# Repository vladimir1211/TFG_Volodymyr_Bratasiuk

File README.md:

# TFG_Volodymyr_Bratasiuk
Este repositorio contiene diseños de las PCBs generados para mi TFG durante la segunda mitad del 2022.

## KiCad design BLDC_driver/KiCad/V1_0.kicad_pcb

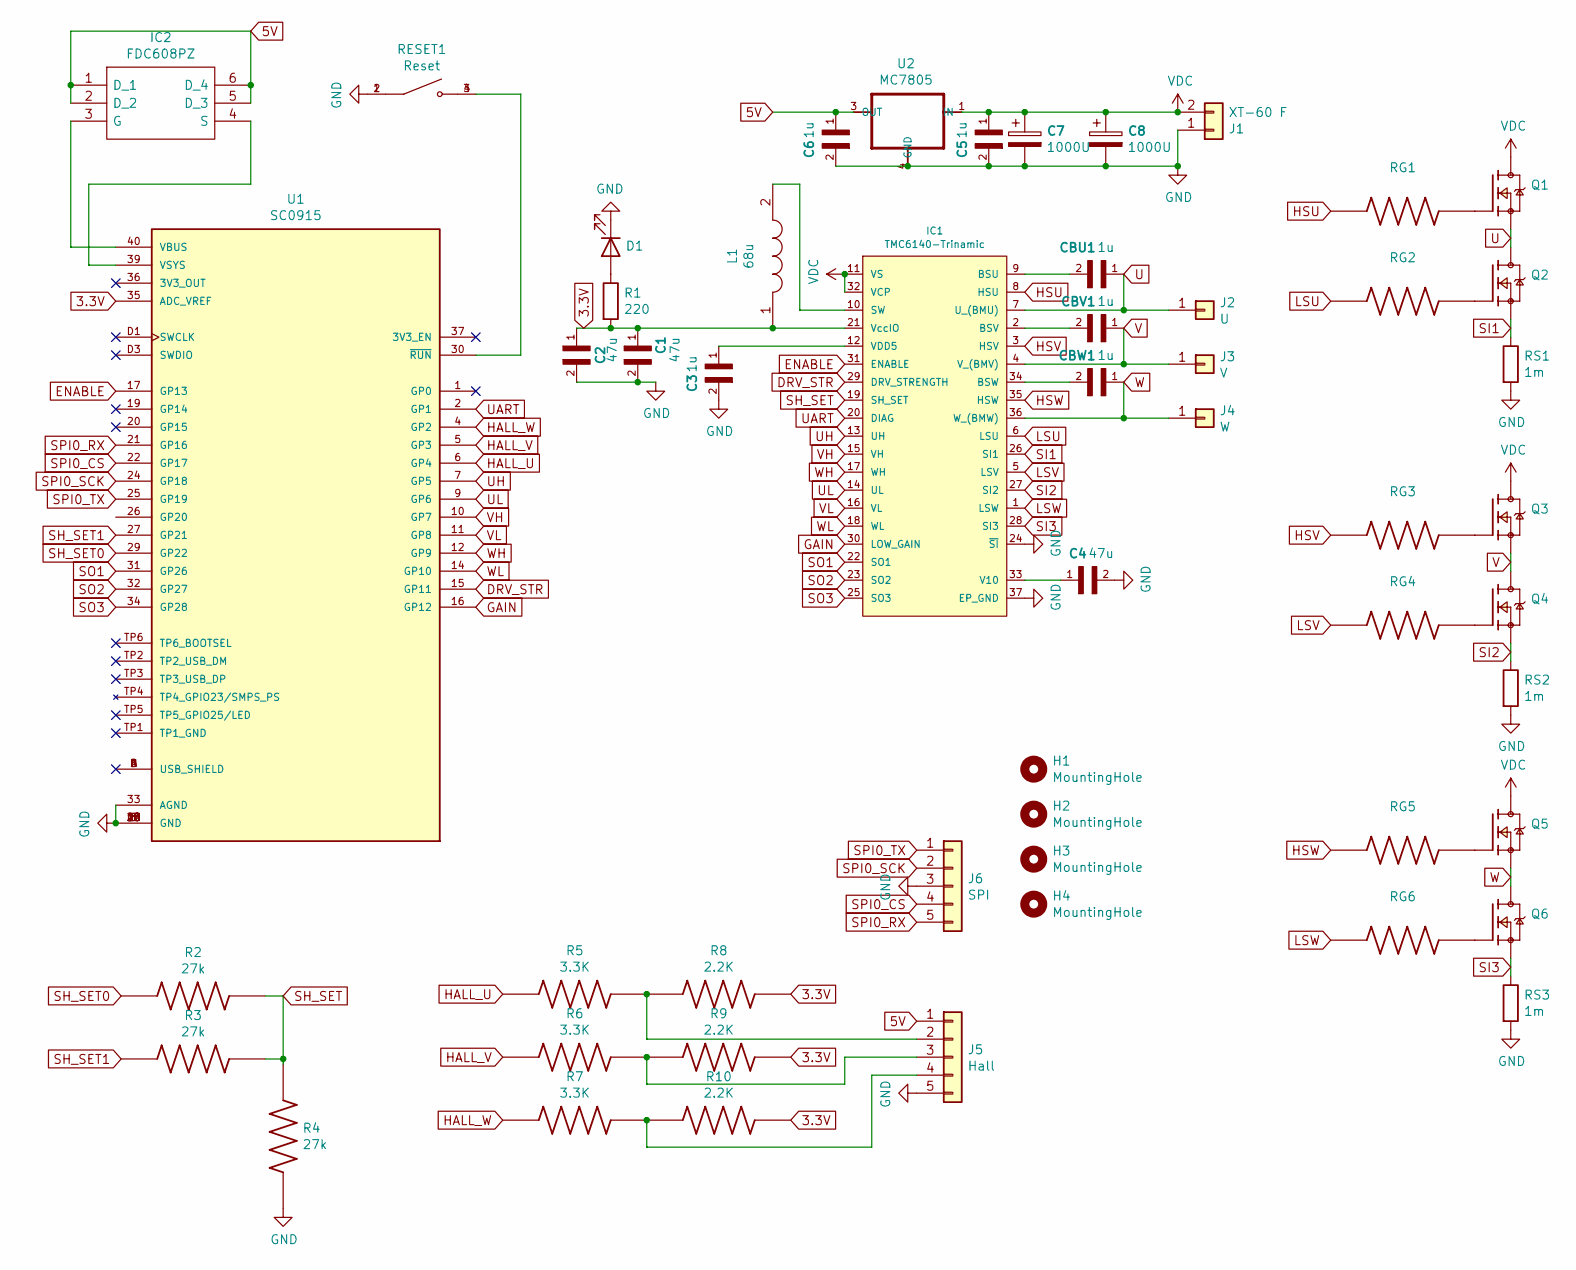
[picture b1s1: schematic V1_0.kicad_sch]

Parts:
C1, C2, C4: 47u; CAPC3225X270N
C3, C5, C6: 1u; CAPC2012X140N
C7, C8: 1000U; CP_Radial_D16.0mm_P7.50mm
CBU1: 1u; CAPC2012X140N
CBV1: 1u; CAPC2012X140N
CBW1: 1u; CAPC2012X140N
D1: LED; LED_D3.0mm
H1, H2, H3, H4: MountingHole; MountingHole_3.2mm_M3
IC1: TMC6140-Trinamic; QFN-36-1EP_5x6mm_P0.5mm_EP3.6x4.1mm_ThermalVias
IC2: FDC608PZ; SOT95P275X110-6N; Manufacturer_Part_Number FDC608PZ
J1: XT-60 F; AMASS_XT60-F_1x02_P7.20mm_Vertical
J2: U; MountingHole_2.2mm_M2_Pad_Via
J3: V; MountingHole_2.2mm_M2_Pad_Via
J4: W; MountingHole_2.2mm_M2_Pad_Via
J5: Hall; PinHeader_1x05_P2.54mm_Vertical
J6: SPI; PinHeader_1x05_P2.54mm_Vertical
L1: 68u; NPIS27H680MTRF; Manufacturer_Part_Number NPIS27H680MTRF
Q1, Q2, Q3, Q4, Q5, Q6: IAUS300N08S5N012ATMA1; IFX-PG-HSOG-8-1-V; PARTREV 1.0
R1: 220; R_Axial_DIN0207_L6.3mm_D2.5mm_P7.62mm_Horizontal
R2, R3, R4: 27k; RESC1508X50N
R5, R6, R7: 3.3K; RESC1608X55N
R8, R9, R10: 2.2K; RESC1608X55N; Voltage_Rating 50 V; Tolerance 1%
RESET1: Reset; SW_1571563-1
RG1, RG2, RG3, RG4, RG5, RG6: CRL1206-FW-1R00ELF; RESC3216X70N
RS1, RS2, RS3: 1m; RESC6331X70N
U1: SC0915; MODULE_SC0915; PARTREV 1.6
U2: MC7805; TO229P990X238-4N

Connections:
3.3V: C1.1, C2.1, IC1.21 (VccIO), L1.1, R1.2, R8.2, R9.2, R10.2, U1.35 (ADC_VREF)
5V: C6.1, IC2.1 (D_1), IC2.2 (D_2), IC2.5 (D_3), IC2.6 (D_4), J5.1, U2.3 (OUT)
DRV_STR: IC1.29 (DRV_STRENGTH), U1.15 (GP11)
ENABLE: IC1.31 (ENABLE), U1.17 (GP13)
GAIN: IC1.30 (LOW_GAIN), U1.16 (GP12)
GND: C1.2, C2.2, C3.2, C4.2, C5.2, C6.2, C7.2, C8.2, D1.1 (K), IC1.24 (~SI), IC1.37 (EP_GND), J1.1, J5.5, J6.3, R4.1, RESET1.1, RESET1.2, RS1.2, RS2.2, RS3.2, U1.3 (GND), U1.8 (GND), U1.13 (GND), U1.18 (GND), U1.23 (GND), U1.28 (GND), U1.33 (AGND), U1.38 (GND), U1.D2 (GND), U2.4 (GND)
HALL_U: R5.1, U1.6 (GP4)
HALL_V: R6.1, U1.5 (GP3)
HALL_W: R7.1, U1.4 (GP2)
HSU: IC1.8 (HSU), RG1.1
HSV: IC1.3 (HSV), RG3.1
HSW: IC1.35 (HSW), RG5.1
LSU: IC1.6 (LSU), RG2.1
LSV: IC1.5 (LSV), RG4.1
LSW: IC1.1 (LSW), RG6.1
unnamed: C3.1, IC1.12 (VDD5)
unnamed: C4.1, IC1.33 (V10)
unnamed: CBU1.2, IC1.9 (BSU)
unnamed: CBV1.2, IC1.2 (BSV)
unnamed: CBW1.2, IC1.34 (BSW)
unnamed: D1.2 (A), R1.1
unnamed: IC1.10 (SW), L1.2
unnamed: IC2.3 (G), U1.40 (VBUS)
unnamed: IC2.4 (S), U1.39 (VSYS)
unnamed: J5.2, R5.2, R8.1
unnamed: J5.3, R6.2, R9.1
unnamed: J5.4, R7.2, R10.1
unnamed: Q1.1, RG1.2
unnamed: Q2.1, RG2.2
unnamed: Q3.1, RG3.2
unnamed: Q4.1, RG4.2
unnamed: Q5.1, RG5.2
unnamed: Q6.1, RG6.2
unnamed: RESET1.3, RESET1.4, U1.30 (~RUN)
SH_SET: IC1.19 (SH_SET), R2.2, R3.2, R4.2
SH_SET0: R2.1, U1.29 (GP22)
SH_SET1: R3.1, U1.27 (GP21)
SI1: IC1.26 (SI1), Q2.2, Q2.3, Q2.4, Q2.5, Q2.6, Q2.7, Q2.8, RS1.1
SI2: IC1.27 (SI2), Q4.2, Q4.3, Q4.4, Q4.5, Q4.6, Q4.7, Q4.8, RS2.1
SI3: IC1.28 (SI3), Q6.2, Q6.3, Q6.4, Q6.5, Q6.6, Q6.7, Q6.8, RS3.1
SO1: IC1.22 (SO1), U1.31 (GP26)
SO2: IC1.23 (SO2), U1.32 (GP27)
SO3: IC1.25 (SO3), U1.34 (GP28)
SPI0_CS: J6.4, U1.22 (GP17)
SPI0_RX: J6.5, U1.21 (GP16)
SPI0_SCK: J6.2, U1.24 (GP18)
SPI0_TX: J6.1, U1.25 (GP19)
U: CBU1.1, IC1.7 (U_(BMU)), J2.1, Q1.2, Q1.3, Q1.4, Q1.5, Q1.6, Q1.7, Q1.8, Q2.9
UART: IC1.20 (DIAG), U1.2 (GP1)
UH: IC1.13 (UH), U1.7 (GP5)
UL: IC1.14 (UL), U1.9 (GP6)
V: CBV1.1, IC1.4 (V_(BMV)), J3.1, Q3.2, Q3.3, Q3.4, Q3.5, Q3.6, Q3.7, Q3.8, Q4.9
VDC: C5.1, C7.1, C8.1, IC1.11 (VS), IC1.32 (VCP), J1.2, Q1.9, Q3.9, Q5.9, U2.1 (IN)
VH: IC1.15 (VH), U1.10 (GP7)
VL: IC1.16 (VL), U1.11 (GP8)
W: CBW1.1, IC1.36 (W_(BMW)), J4.1, Q5.2, Q5.3, Q5.4, Q5.5, Q5.6, Q5.7, Q5.8, Q6.9
WH: IC1.17 (WH), U1.12 (GP9)
WL: IC1.18 (WL), U1.14 (GP10)

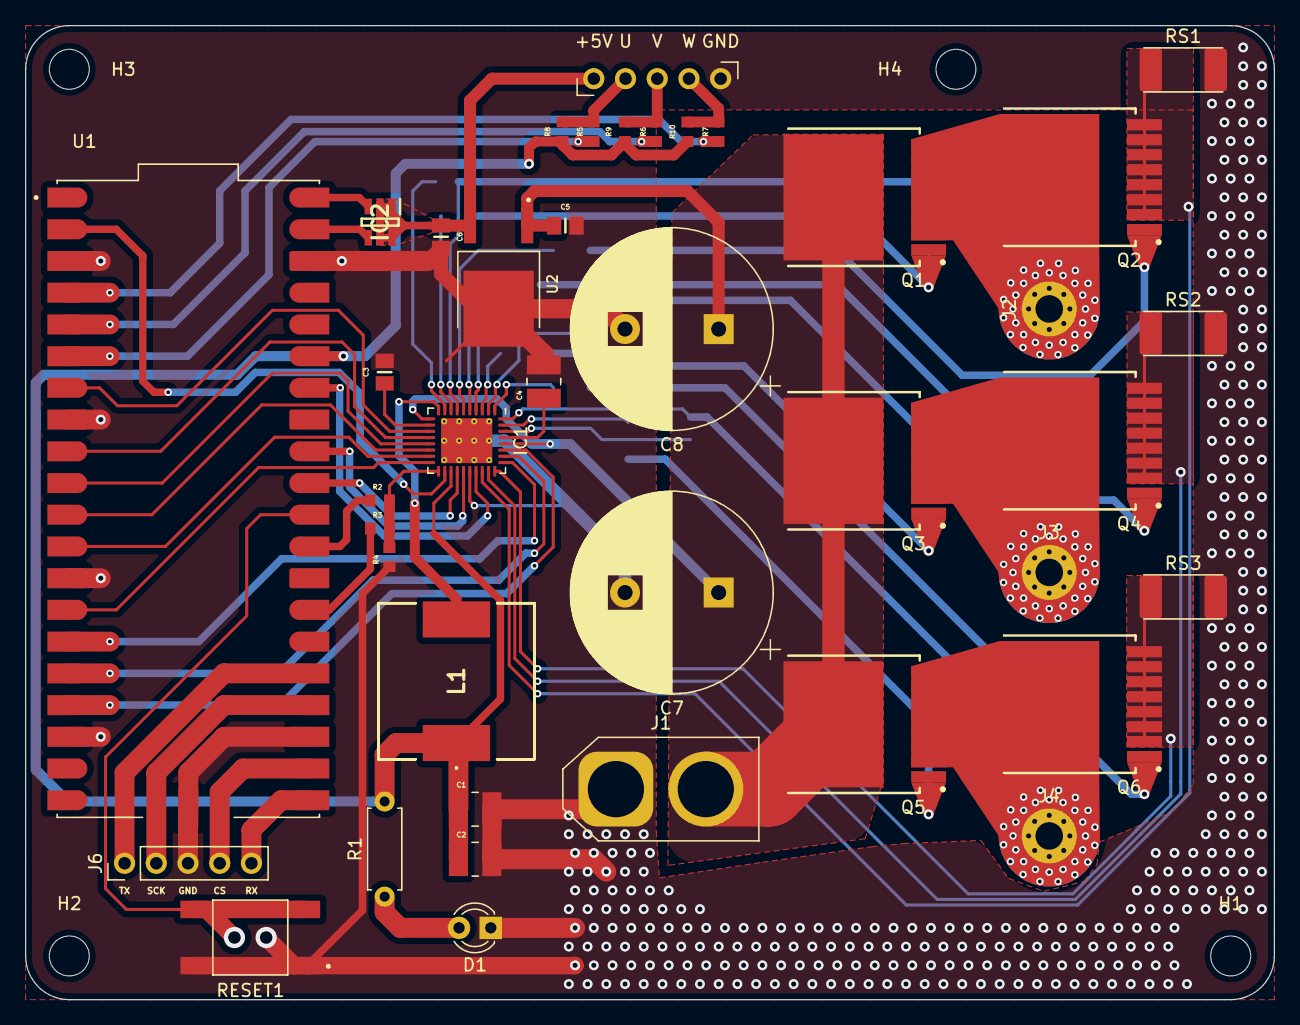
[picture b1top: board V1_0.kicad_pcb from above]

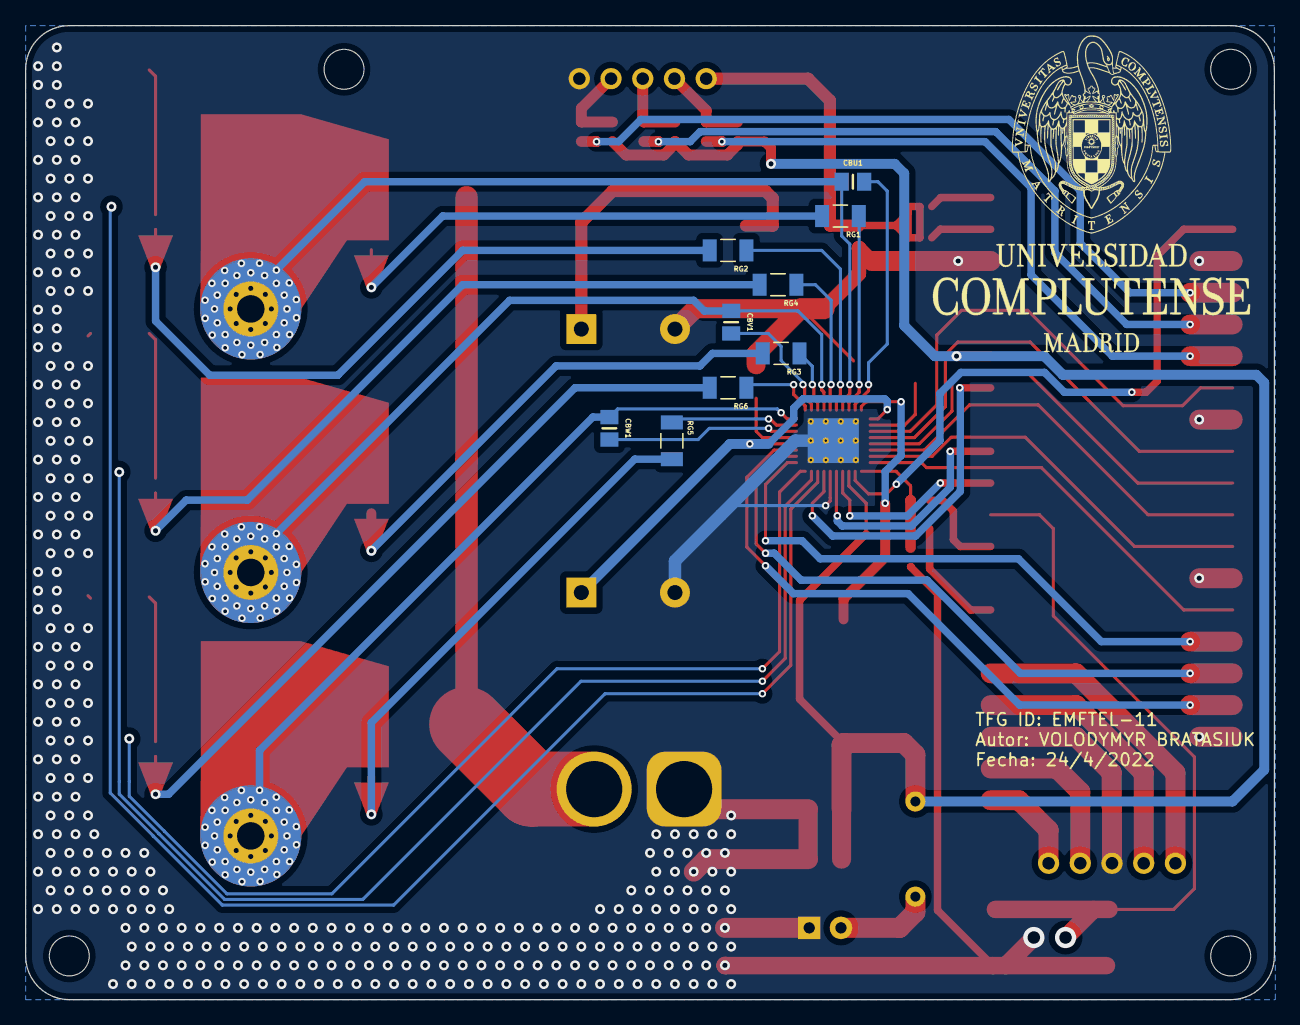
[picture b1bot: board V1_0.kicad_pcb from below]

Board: 2 copper layers, 100.0 x 78.0 mm, 53 parts (9 on the bottom side), 58 nets.

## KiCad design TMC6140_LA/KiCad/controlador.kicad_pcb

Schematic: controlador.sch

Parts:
IC1: TMC6140-Trinamic; QFN-36-1EP_5x6mm_P0.5mm_EP3.6x4.1mm_ThermalVias
J1, J2: Conn_01x19; PinHeader_1x19_P2.54mm_Vertical

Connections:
1: IC1.1, J1.1
2: IC1.2, J1.2
3: IC1.3, J1.3
4: IC1.4, J1.4
5: IC1.5, J1.5
6: IC1.6, J1.6
7: IC1.7, J1.7
8: IC1.8, J1.8
9: IC1.9, J1.9
10: IC1.10, J1.10
11: IC1.11, J1.11
12: IC1.12, J1.12
13: IC1.13, J1.13
14: IC1.14, J1.14
15: IC1.15, J1.15
16: IC1.16, J1.16
17: IC1.17, J1.17
18: IC1.18, J1.18
19: IC1.19, J2.19
20: IC1.20, J2.18
21: IC1.21, J2.17
22: IC1.22, J2.16
23: IC1.23, J2.15
24: IC1.24, J2.14
25: IC1.25, J2.13
26: IC1.26, J2.12
27: IC1.27, J2.11
28: IC1.28, J2.10
29: IC1.29, J2.9
30: IC1.30, J2.8
31: IC1.31, J2.7
32: IC1.32, J2.6
33: IC1.33, J2.5
34: IC1.34, J2.4
35: IC1.35, J2.3
36: IC1.36, J2.2
GND: IC1.37, J1.19, J2.1

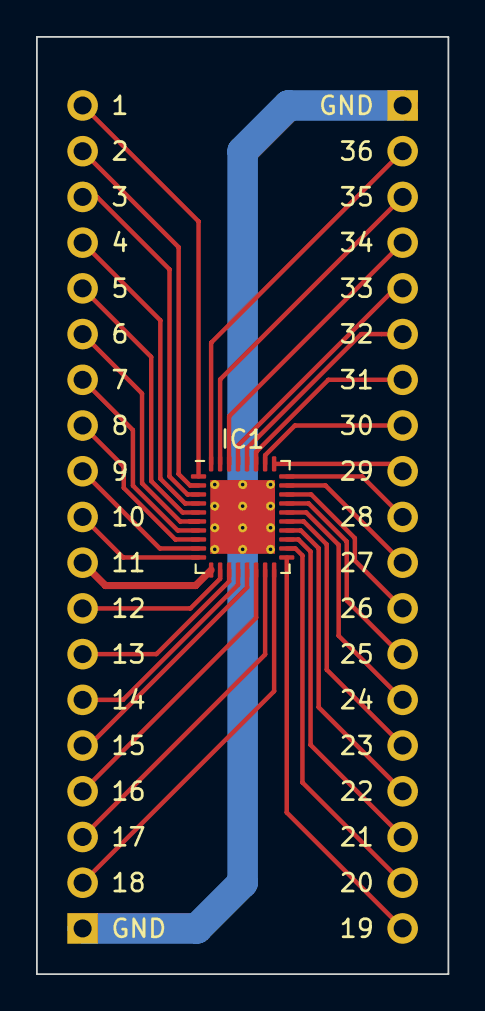
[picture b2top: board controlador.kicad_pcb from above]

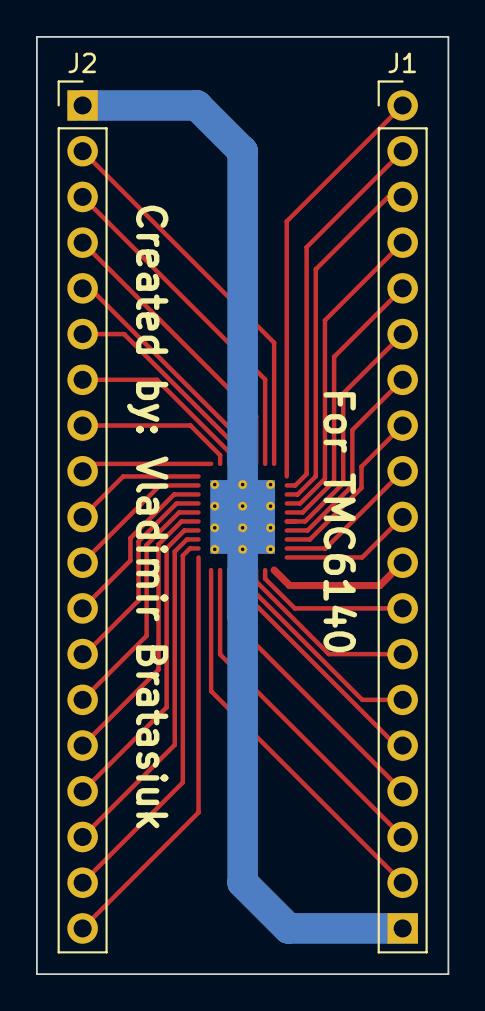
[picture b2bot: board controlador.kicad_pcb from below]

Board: 2 copper layers, 22.9 x 52.1 mm, 3 parts (2 on the bottom side), 37 nets.

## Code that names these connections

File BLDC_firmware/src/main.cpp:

// Motor phases pins
//-----------------------------------------------------------------------------
#define HU  5   // High-side switch U
#define LU  6   // Low-side switch U
#define HV  7   // High-side switch V
#define LV  8   // Low-side switch V
#define HW  9   // High-side switch W
#define LW  10  // Low-side switch W
//-----------------------------------------------------------------------------

// Hall sensor pins
//-----------------------------------------------------------------------------
#define HALL_U 2  // Hall sensor phase U
#define HALL_V 3  // Hall sensor phase V
#define HALL_W 4  // Hall sensor phase W
//-----------------------------------------------------------------------------

// Pins for aditional control of TMC6140-LA
//-----------------------------------------------------------------------------
#define DRV_STR 11      //Set to 1: 0.5A / Set to 0: 1A
#define GAIN 12         //Set to 1: gain 50x / Set to 0: gain 20x
#define ENABLE_PIN 13   //Set to 1: enable / Set to 0: disable
#define SH_0 22         //Set to 1: short to ground / Set to 0: no short
#define SH_1 21         //Set to 1: short to ground / Set to 0: no short
//------------------------------------------------------------------------------

//
#define PP 15 // Pole pairs
//
#define LED 25 // LED pin

#include <SimpleFOC.h>


// Hall sensor instance
// HallSensor(int hallA, int hallB , int cpr, int index)
//  - hallA, hallB, hallC    - HallSensor A, B and C pins
//  - pp                     - pole pairs
HallSensor sensor = HallSensor(HALL_U, HALL_V, HALL_W, PP);

// Interrupt routine intialisation
// channel A and B callbacks
void doA(){sensor.handleA();}
void doB(){sensor.handleB();}
void doC(){sensor.handleC();}

// BLDC driver instance
//  BLDCDriver6PWM( int phA_h, int phA_l, int phB_h, int phB_l, int phC_h, int phC_l, int en)
//  - phA_h, phA_l - A phase pwm pin high/low pair 
//  - phB_h, phB_l - B phase pwm pin high/low pair
//  - phB_h, phC_l - C phase pwm pin high/low pair
//  - enable pin    - (optional input)
BLDCDriver6PWM driver = BLDCDriver6PWM(HU, LU, HV, LV, HW, LW, ENABLE_PIN);
// BLDCMotor motor = BLDCMotor(pole pair number);
BLDCMotor motor = BLDCMotor(PP);

// velocity set point variable
float target_velocity = 5;
// include commander interface
Commander command = Commander(Serial);
void doMotor(char* cmd) { command.motor(&motor, cmd); }


void receiveEvent(int bytes) {

  digitalWrite(LED, HIGH);
  

  int x = Wire.read();    // read one character from the I2C
  
  motor.move(x);

  Serial.print( x);
  Serial.print( "\n");
  digitalWrite(LED, LOW);
}
void seti2c() {
  // Define the LED pin as Output
  pinMode (LED, OUTPUT);
  delay(500);
  // Start the I2C Bus as Slave on address 9
  Wire.begin(9); 
  // Attach a function to trigger when something is received.
  Wire.onReceive(receiveEvent);
}

void mode0() {
  // Set the motor to mode 0
  motor.PID_velocity.P = 0.1;
  motor.PID_velocity.I = 0.5;
  motor.PID_velocity.D = 0;
  motor.voltage_limit = 4;
  Serial.print("MODE 0 SET\n");
}

void mode1() {
  // Set the motor to mode 1
  motor.PID_velocity.P = 0.3;
  motor.PID_velocity.I = 1;
  motor.PID_velocity.D = 0;
  motor.voltage_limit = 8;
  Serial.print("MODE 1 SET\n");
}

void mode2() {
  // Set the motor to mode 2
  motor.PID_velocity.P = 0.9;
  motor.PID_velocity.I = 2;
  motor.PID_velocity.D = 0;
  motor.voltage_limit = 10;
  Serial.print("MODE 2 SET\n");
}

void change_mode(char* cmd) {
  if (cmd[0] == '0') {
    mode0();
  } else if (cmd[0] == '1') {
    mode1();
  } else if (cmd[0] == '2') {
    mode2();
  }
}

void disable_enable(char* cmd) {
  if (cmd[0] == '0') {
    digitalWrite(SH_0, LOW);
    digitalWrite(SH_1, LOW);
    motor.linkSensor(nullptr);
    
    // motor.move(0);
    Serial.print("DISABLE\n");
  } else if (cmd[0] == '1') {
    digitalWrite(SH_0, HIGH);
    digitalWrite(SH_1, HIGH);
    motor.linkSensor(&sensor);
    Serial.print("ENABLE\n");
  }
}


void setup(){

seti2c();

pinMode(DRV_STR, OUTPUT);
pinMode(GAIN, OUTPUT);
pinMode(ENABLE_PIN, OUTPUT);
pinMode(SH_0, OUTPUT);
pinMode(SH_1, OUTPUT);

digitalWrite(ENABLE_PIN, HIGH);
digitalWrite(DRV_STR, LOW);
digitalWrite(GAIN, LOW);
digitalWrite(SH_0, HIGH);
digitalWrite(SH_1, HIGH);

// Serial configuration
//-----------------------------------------------------------------------------
Serial.begin(115200); // 115200 baud rate
delay(10);
Serial.print("Serial ready.\n");
//-----------------------------------------------------------------------------

// Hall sensor configuration
//-----------------------------------------------------------------------------
// check if you need internal pullups
sensor.pullup = Pullup::USE_EXTERN;
// initialise encoder hardware
sensor.init();
// hardware interrupt enable
sensor.enableInterrupts(doA, doB, doC);
Serial.print("Hall sensor configuration done.\n");
//------------------------------------------------------------------------------

// Driver configuration
//------------------------------------------------------------------------------
// power supply voltage [V]
driver.voltage_power_supply = 24.0;

driver.init();
// link the motor and the driver
motor.linkDriver(&driver);

motor.linkSensor(&sensor);



// set control loop type to be used
motor.controller = MotionControlType::velocity;

motor.torque_controller = TorqueControlType::voltage;

motor.foc_modulation = FOCModulationType::SpaceVectorPWM;

// velocity PI controller parameters
// default P=0.5 I = 10
motor.PID_velocity.P = 0.1;
motor.PID_velocity.I = 0.5;
motor.PID_velocity.D = 0;
motor.PID_velocity.output_ramp = 0;

motor.PID_velocity.limit = 20;
//default voltage_power_supply
motor.voltage_limit = 10;

// velocity low pass filtering
// default 5ms - try different values to see what is the best. 
// the lower the less filtered
motor.LPF_velocity.Tf = 0.3;
  

motor.useMonitoring(Serial);
motor.monitor_downsample = 100; // disable monitor at first - optional

// initialize motor
motor.init();
// align sensor and start FOC
//motor.initFOC(zero_electric_offset, sensor_direction);
motor.initFOC(2.09,Direction::CCW);
//------------------------------------------------------------------------------

command.add('M',doMotor,"target setting");

command.add('C', change_mode, "Change control mode");

command.add('D', disable_enable, "Disable motor-0 Enable motor-1");

// monitoring port
Serial.println("Motor ready.");
Serial.println("Set the target velocity using serial terminal:");
delay(10);

motor.move(2);

}
void loop(){
  
  // main FOC algorithm function
  motor.loopFOC();

  // Motion control function
  motor.move();


  motor.monitor();

  // user communication
  command.run();


}
